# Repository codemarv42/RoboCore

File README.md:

# RoboCore

The RoboCore is basically a dual PCB solution, which is mounted on a chassis and takes over the evaluation and control of sensors and motors. Furthermore, this project was created by several people to develop the best robot for the RoboCup in the Rescue Line division. 

# Hardware

A combination of two PCBs is used as our hardware, where the main PCB (RoboCoreV3.2) is plugged onto a Raspberry Pi and therefore forms the main control unit. The second circuit board (RoboLightV4.2) is installed on the underside of the robot and is responsible for measuring the light values on the line track. Below is our current hardware combination.

## To do list

- [x] Find Upload issue
- [x] Implement Boot and EN Buttons
- [x] Find ADC issue when using Neopixel LEDs
- [x] Voltage state LEDs
- [x] Inconsistent red-green difference of the LEDs

## Changelog

RoboCore:

- V3.2: Remove Neopixel led because of ADC problems, better voltage regulator for motor driver and further power management features
- V3.1: Raspberry PI hat design, external Display and buttons as user interface, ESP32-S3, two motor driver, Neopixel LED, Voltage regulator update
- V2: MPU6050 as secound PCB, dual light sensor bar, Pullup Fix near buttons
- V1: Inital Version

RoboLight:

- V4.3: Swap FCP pinout
- V4.2: Use regular RGB LEDs instead, better LED and phototransistor arrangement
- V4.1: Use Neopixel RGB LEDs instead, remove center photo transistor
- V3: Control Leds individual via a shiftregister
- V2: Fix distance between inner photo transistors
- V1: Inital Version

## Control unit PCB

Parameter for PCB (RoboCoreV3.2):

- Layer: 4
- Thickness: 1,6mm
- Length: 65,05mm
- Height: 56,03mm
- Minimum Copper Trace Width: 0,125mm

Pinout:

## Light sensors PCB

Parameter for PCB (RoboLightV4.3):

- Layer: 2
- Thickness: 1,2mm / 1,6mm
- Length: 72,0mm
- Height: 15,23mm
- Minimum Copper Trace Width: 0,15mm

# Software

### You can find instructions for RoboCore V3.2 in PDF format here:
https://github.com/codemarv42/RoboCore/blob/main/Hardware/RoboCoreV3.2/RoboCoreV3.2%20Manual.pdf

## Required libraries

- Adafruit_GFX.h - https://github.com/adafruit/Adafruit-GFX-Library
- Adafruit_BusIO.h - https://github.com/adafruit/Adafruit_BusIO/tree/master
- Adafruit_PWMServoDriver.h - https://github.com/adafruit/Adafruit-PWM-Servo-Driver-Library
- Adafruit_SSD1306.h - https://github.com/adafruit/Adafruit_SSD1306
- MPU6050_light.h - https://github.com/rfetick/MPU6050_light
- VL53L1X.h - https://github.com/pololu/vl53l1x-arduino

## Download Mode

If no program can be uploaded to the ESP32-S3, it must be set to download mode. The following steps are necessary to do this:

1. Press and hold the BOOT and RESET button
2. Connect the RoboCore to the computer via USB
3. Release the RESET button while still holding the BOOT button
4. Release the BOOT button after a few seconds

## Compilation settings

To compile your program and then upload it to the RoboCore, some steps are necessary:

1. First you have to install the kernel of the ESP32 in Arduino: https://docs.espressif.com/projects/arduino-esp32/en/latest/installing.html
2. Next, the compilation settings must be specified. To do this, first select "ESP32S3 Dev Module" under Tools --> Board.
3. In the last step, the parameters of the ESP32 on the RoboCore must be set. To do this, select the following under Tools: 
- Board: "ESP32S3 Dev Module"
- USB CDC On Boot: "Enabled"
- CPU Frequency: "240MHz (WiFi/BT)"
- Flash Mode: "QIO 120MHz"
- Flash Size: "8MB (32Mb)"
- Partition Scheme: "8MB with SPIFFS"
- Erase all flash: "Disabled"
- Upload Speed: "921600"

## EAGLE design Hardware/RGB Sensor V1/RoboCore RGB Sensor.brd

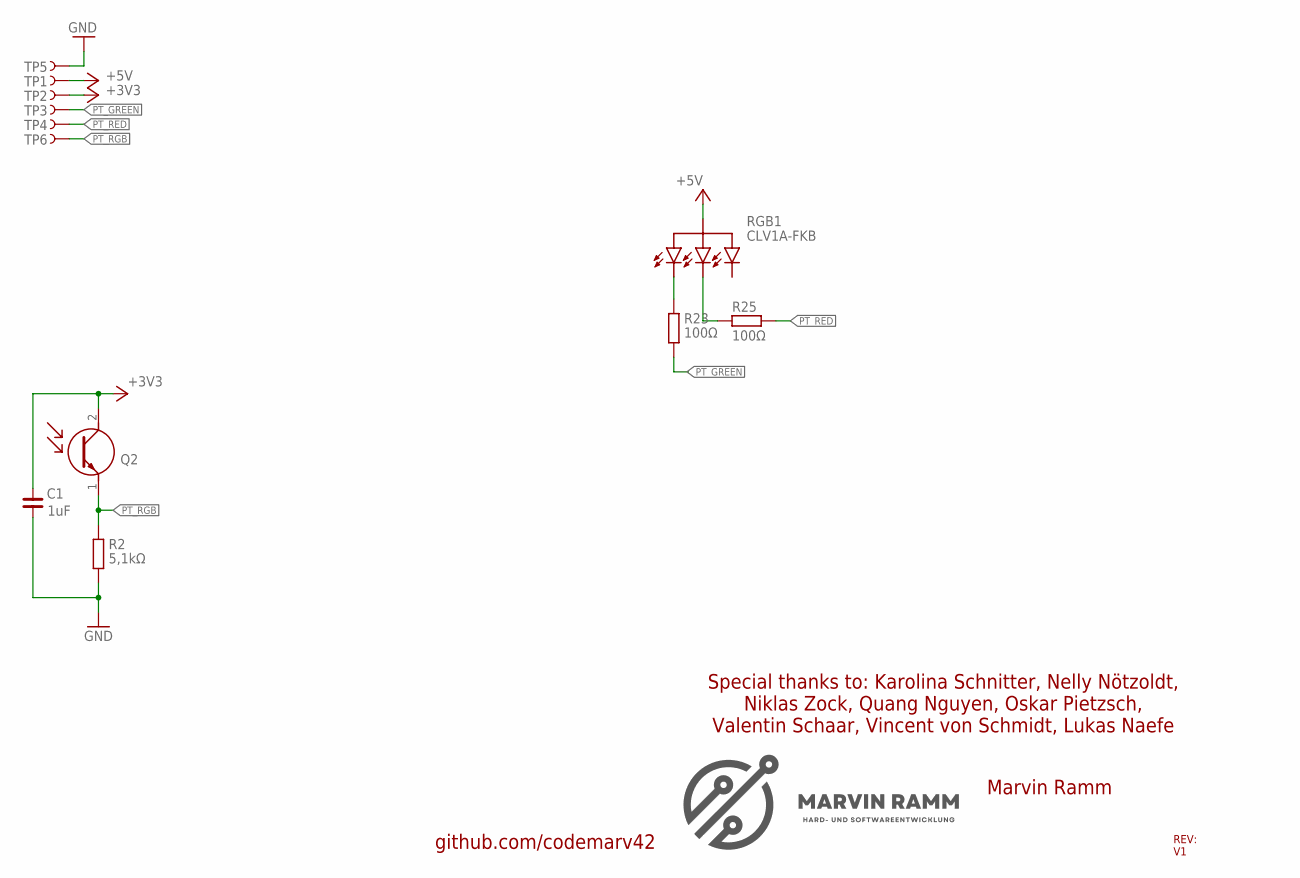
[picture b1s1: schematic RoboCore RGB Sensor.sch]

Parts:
C1: 1uF; C0402
Q2: PT17-21C/L41/TR8; 0805
R2: 5,1kΩ; R0402
R23, R25: 100Ω; R0402
RGB1: RGBLED
TP1, TP2, TP3, TP4, TP5, TP6: TEST-POINT3X5; PAD.03X.05

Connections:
+3V3: C1.2, Q2.2 (C), TP2.1
+5V: RGB1.+5V, TP1.1
GND: C1.1, R2.2, TP5.1
unnamed: R23.1, RGB1.P3
unnamed: R25.1, RGB1.P2
PT_GREEN: R23.2, TP3.1
PT_RED: R25.2, TP4.1
PT_RGB: Q2.1 (E), R2.1, TP6.1

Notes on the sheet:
RGB1
CLV1A-FKB
Marvin Ramm
REV: V1
github.com/codemarv42
Special thanks to: Karolina Schnitter, Nelly Nötzoldt, Niklas Zock, Quang Nguyen, Oskar Pietzsch, Valentin Schaar, Vincent von Schmidt, Lukas Naefe

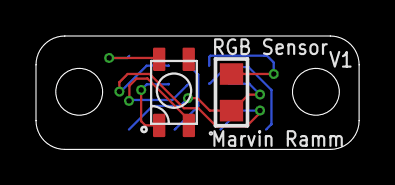
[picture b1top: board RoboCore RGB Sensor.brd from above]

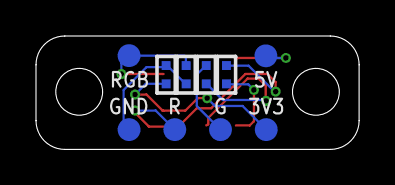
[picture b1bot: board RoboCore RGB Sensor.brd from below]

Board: 2 copper layers, 17.9 x 6.3 mm, 12 parts (10 on the bottom side), 8 nets.

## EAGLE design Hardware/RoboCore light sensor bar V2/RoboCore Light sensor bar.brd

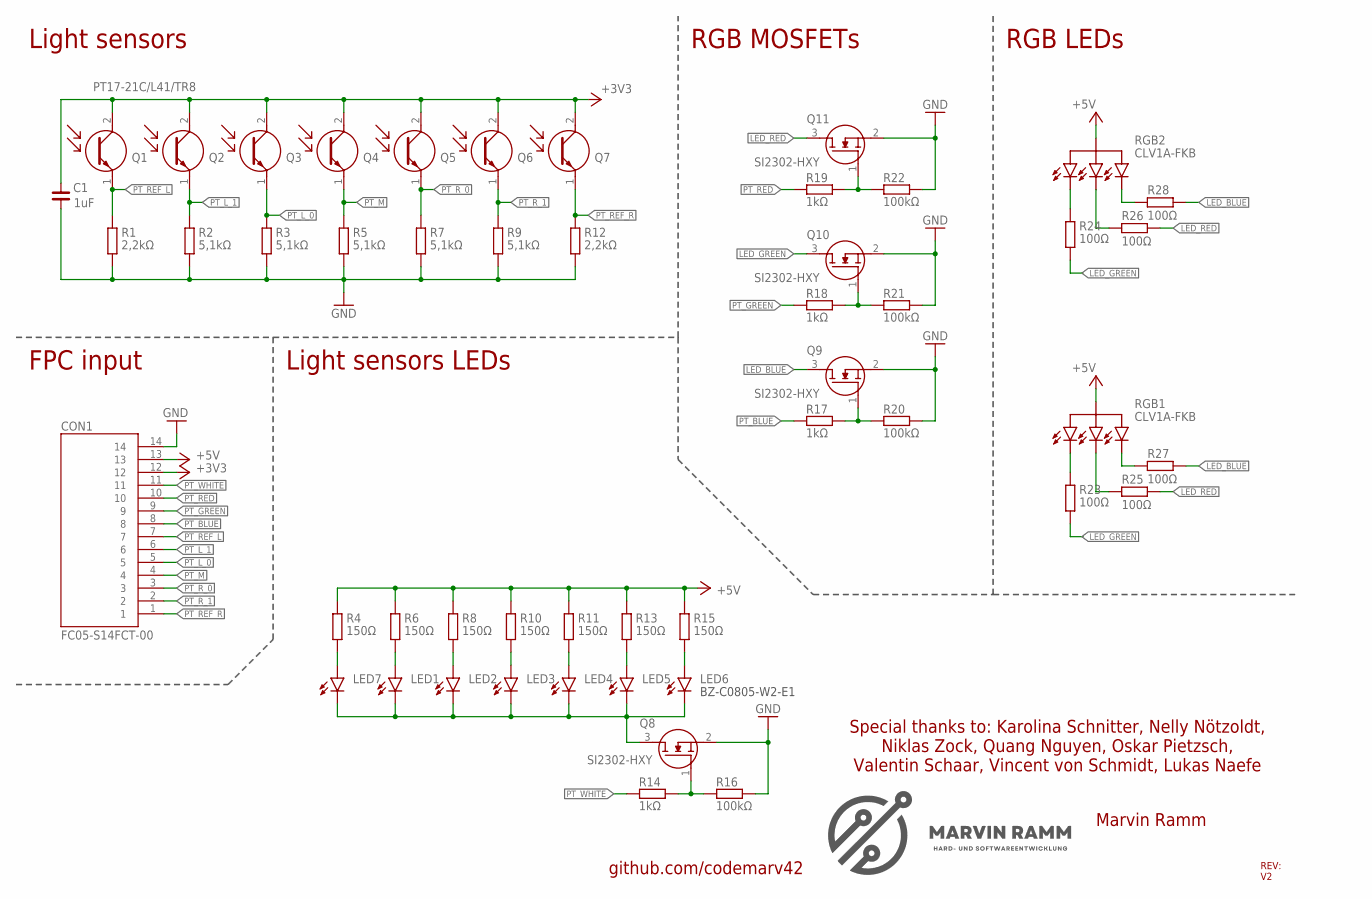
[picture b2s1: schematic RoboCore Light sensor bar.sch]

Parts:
C1: 1uF; C0402
CON1: FC05-S14FCT-00
LED1, LED2, LED3, LED4, LED5, LED6, LED7: LEDCHIP-LED0805; CHIP-LED0805
Q1, Q2, Q3, Q4, Q5, Q6, Q7: PT17-21C/L41/TR8; 0805
Q8, Q9, Q10, Q11: SI2302DDS-T1-GE3; SOT95P237X112-3N
R1, R12: 2,2kΩ; R0402
R2, R3, R5, R7, R9: 5,1kΩ; R0402
R4, R6, R8, R10, R11, R13, R15: 150Ω; R0402
R14, R17, R18, R19: 1kΩ; R0402
R16, R20, R21, R22: 100kΩ; R0402
R23, R24, R25, R26, R27, R28: 100Ω; R0402
RGB1, RGB2: RGBLED

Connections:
+3V3: C1.2, CON1.12, Q1.2 (C), Q2.2 (C), Q3.2 (C), Q4.2 (C), Q5.2 (C), Q6.2 (C), Q7.2 (C)
+5V: CON1.13, R4.1, R6.1, R8.1, R10.1, R11.1, R13.1, R15.1, RGB1.+5V, RGB2.+5V
GND: C1.1, CON1.14, Q8.2 (S), Q9.2 (S), Q10.2 (S), Q11.2 (S), R1.2, R2.2, R3.2, R5.2, R7.2, R9.2, R12.2, R16.2, R20.2, R21.2, R22.2
LED_BLUE: Q9.3 (D), R27.2, R28.2
LED_GREEN: Q10.3 (D), R23.2, R24.2
LED_RED: Q11.3 (D), R25.2, R26.2
unnamed: LED1.C, LED2.C, LED3.C, LED4.C, LED5.C, LED6.C, LED7.C, Q8.3 (D)
unnamed: LED7.A, R4.2
unnamed: Q11.1 (G), R19.2, R22.1
unnamed: Q10.1 (G), R18.2, R21.1
unnamed: Q9.1 (G), R17.2, R20.1
unnamed: LED5.A, R13.2
unnamed: LED6.A, R15.2
unnamed: Q8.1 (G), R14.2, R16.1
unnamed: LED4.A, R11.2
unnamed: R24.1, RGB2.P3
unnamed: R28.1, RGB2.P1
unnamed: R26.1, RGB2.P2
unnamed: R23.1, RGB1.P3
unnamed: R27.1, RGB1.P1
unnamed: R25.1, RGB1.P2
unnamed: LED3.A, R10.2
unnamed: LED2.A, R8.2
unnamed: LED1.A, R6.2
PT_BLUE: CON1.8, R17.1
PT_GREEN: CON1.9, R18.1
PT_L_0: CON1.5, Q3.1 (E), R3.1
PT_L_1: CON1.6, Q2.1 (E), R2.1
PT_M: CON1.4, Q4.1 (E), R5.1
PT_RED: CON1.10, R19.1
PT_REF_L: CON1.7, Q1.1 (E), R1.1
PT_REF_R: CON1.1, Q7.1 (E), R12.1
PT_R_0: CON1.3, Q5.1 (E), R7.1
PT_R_1: CON1.2, Q6.1 (E), R9.1
PT_WHITE: CON1.11, R14.1

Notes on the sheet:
Light sensors
RGB2
CLV1A-FKB
RGB1
Light sensors LEDs
SI2302-HXY
Marvin Ramm
REV: V2
github.com/codemarv42
FPC input
RGB MOSFETs
RGB LEDs
Special thanks to: Karolina Schnitter, Nelly Nötzoldt, Niklas Zock, Quang Nguyen, Oskar Pietzsch, Valentin Schaar, Vincent von Schmidt, Lukas Naefe
BZ-C0805-W2-E1

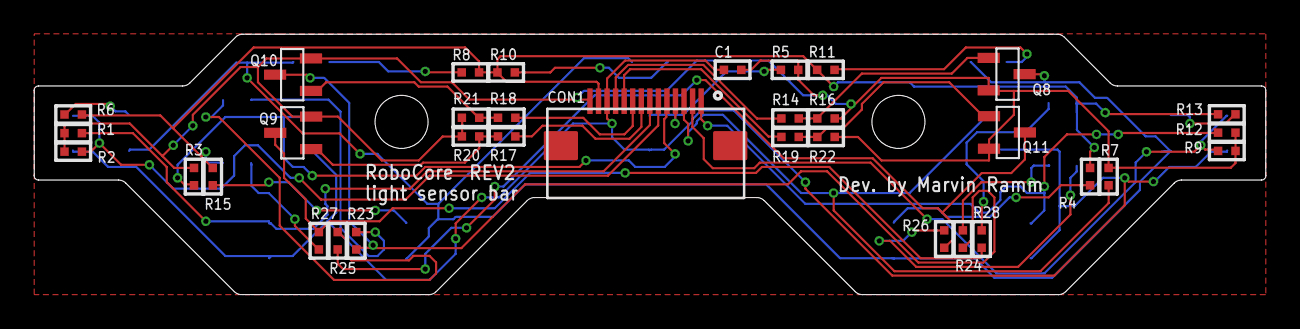
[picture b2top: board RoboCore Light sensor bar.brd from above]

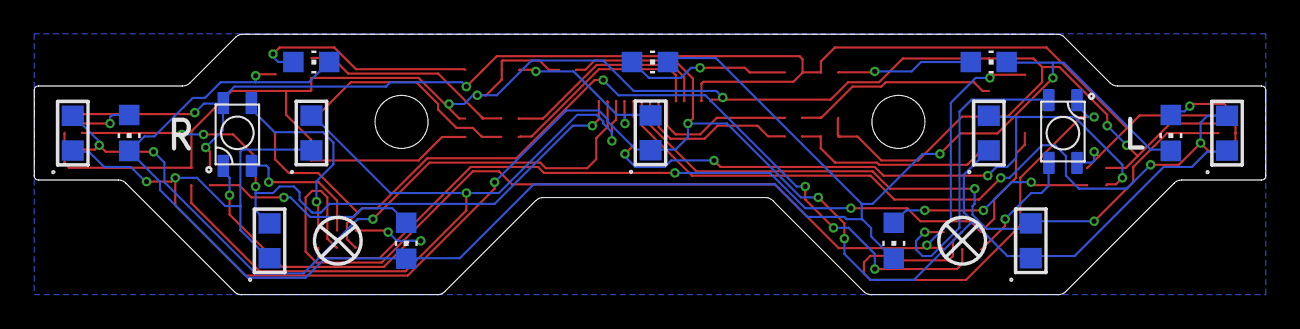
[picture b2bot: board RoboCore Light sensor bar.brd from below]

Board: 2 copper layers, 72.0 x 15.2 mm, 50 parts (16 on the bottom side), 35 nets.

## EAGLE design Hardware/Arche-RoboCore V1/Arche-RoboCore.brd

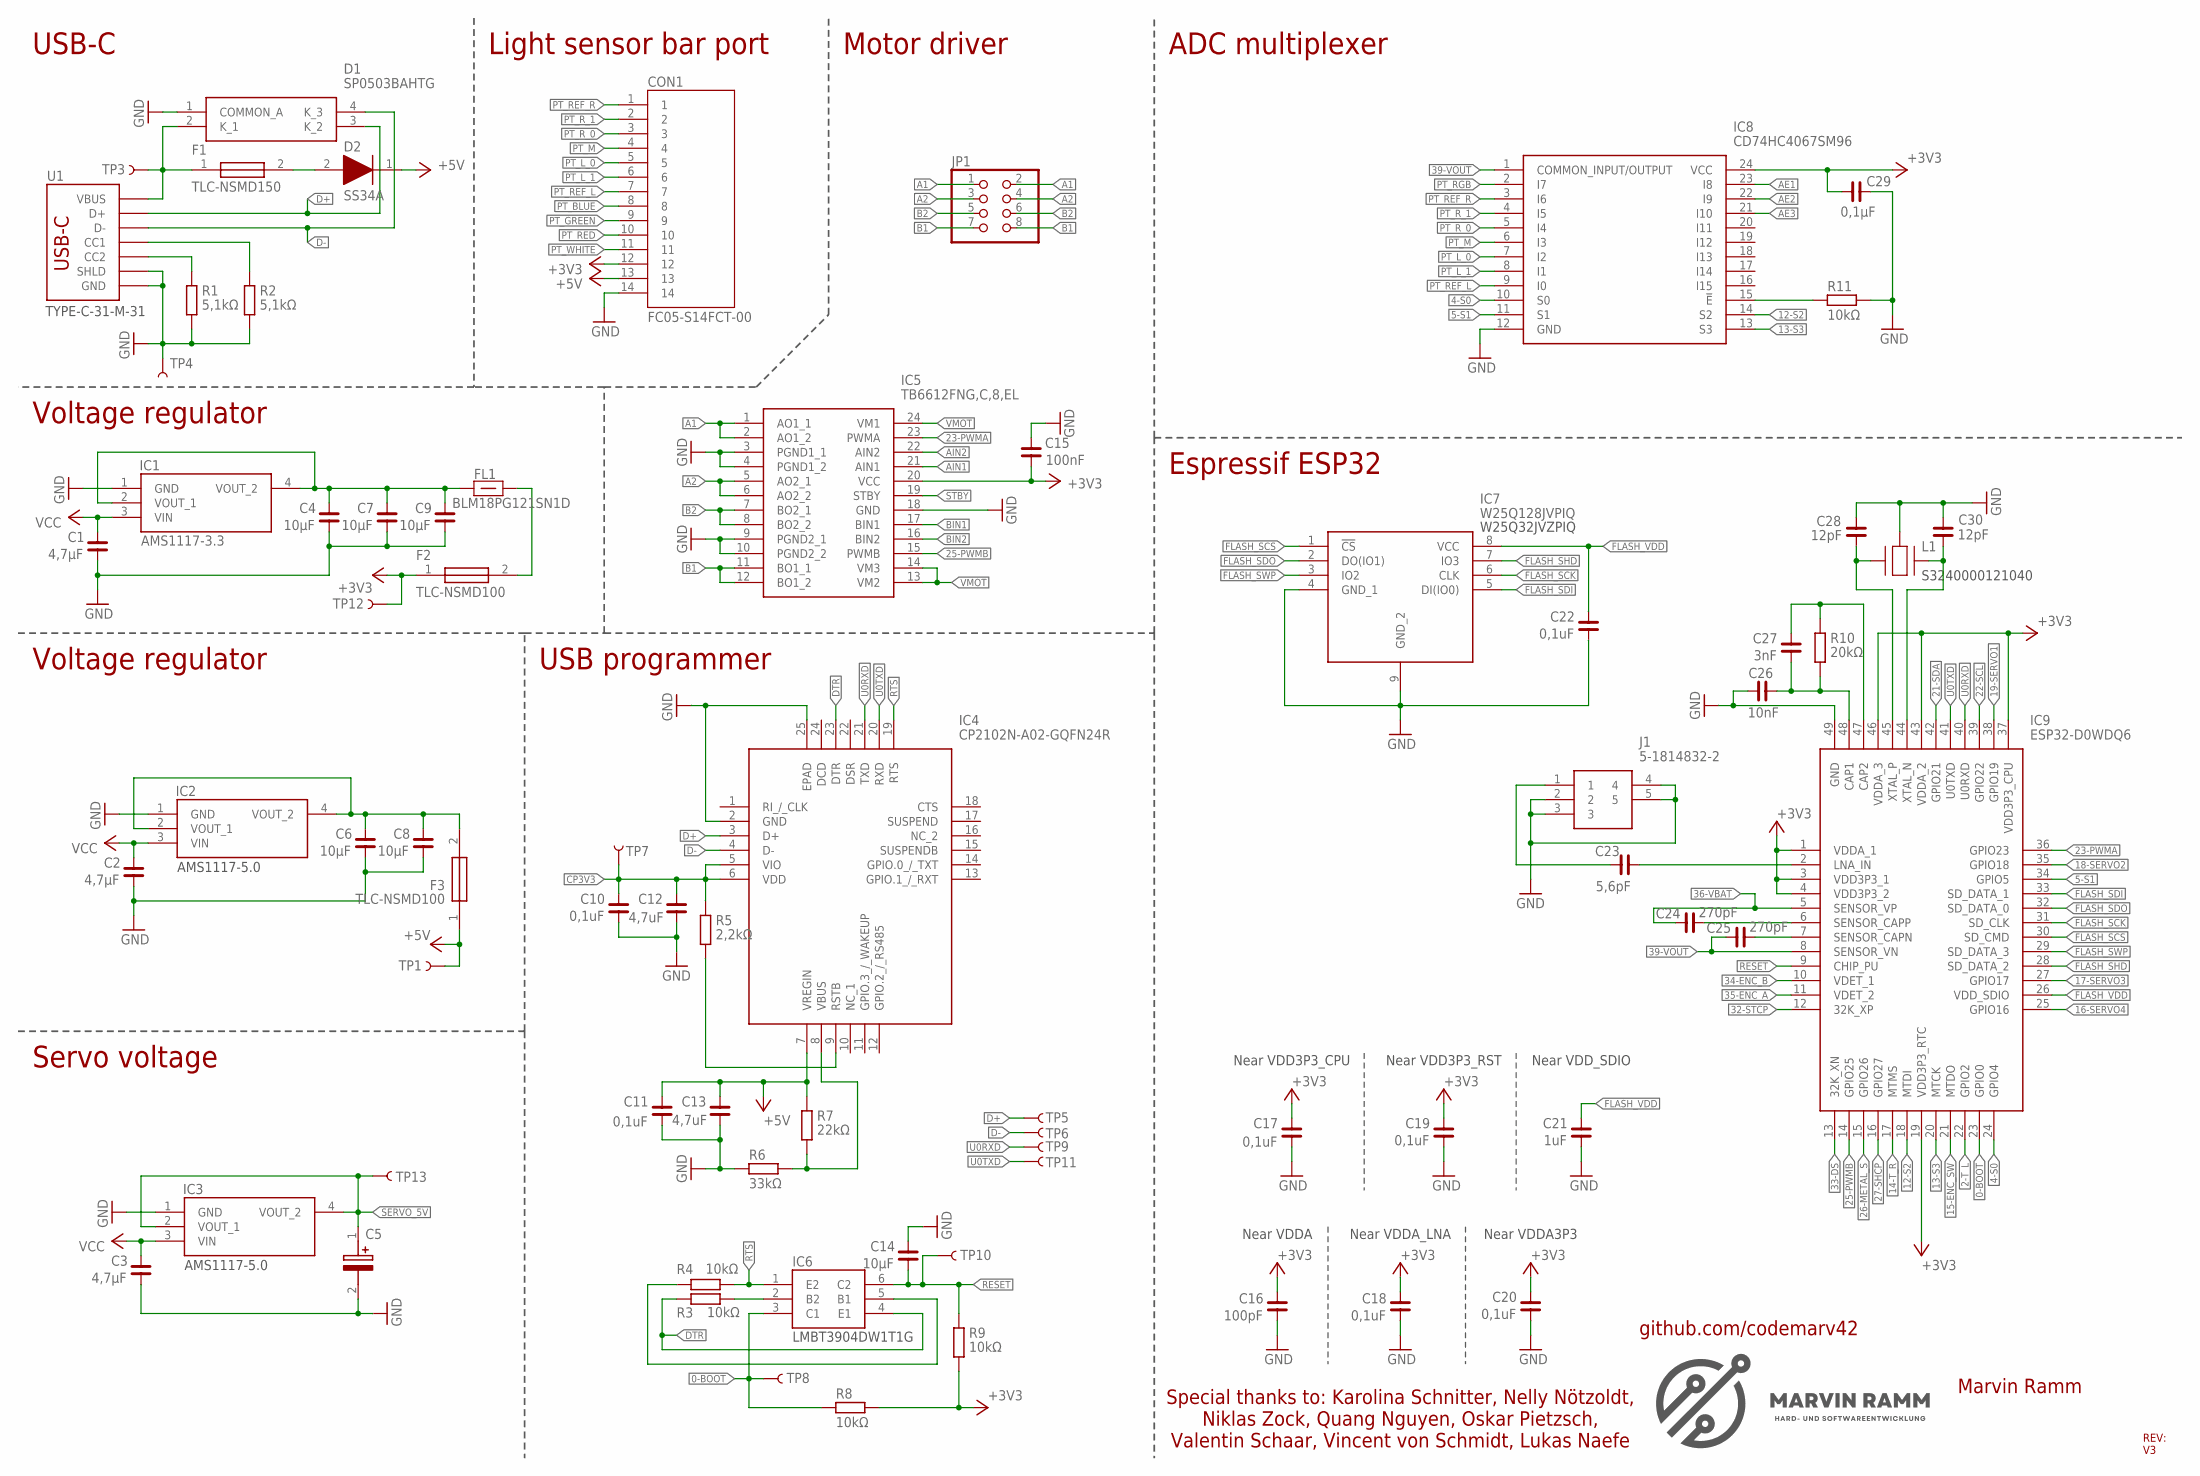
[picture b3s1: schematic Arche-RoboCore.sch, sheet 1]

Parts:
C1, C2, C3: 4,7µF; C0603
C4, C6, C7, C8, C9, C14: 10µF; C0603
C5: UUD1C151MCL1GS; CAPAE660X800N
C10, C11, C17, C18, C19, C20, C22: 0,1uF; C0402
C12, C13: 4,7uF; C0402
C15: 100nF; C0402
C16: 100pF; C0402
C21: 1uF; C0402
C23: 5,6pF; C0402
C24, C25: 270pF; C0402
C26: 10nF; C0402
C27: 3nF; C0402
C28, C30: 12pF; C0402
C29: 0,1µF; C0402
CON1: FC05-S14FCT-00
D1: SP0503BAHTG
D2: SS34A; DIOM5026X262N
F1, F2, F3: NANOSMDC020F-2; FUSC3216X82N
FL1: BLM18PG121SN1D; BLM18AG102BH1D
IC1, IC2, IC3: AMS1117-3.3; SOT229P700X180-4N
IC4: CP2102N-A02-GQFN24R; QFN50P400X400X80-25N
IC5: TB6612FNG,C,8,EL; SOP65P760X160-24N
IC6: MMDT3904-TP; SOT65P230X120-6N
IC7: W25Q128JVPIQ; SON127P800X600X80-9N
IC8: CD74HC4067SM96; SOP65P780X200-24N
IC9: ESP32-D0WDQ6; QFN40P600X600X90-49N
J1: 5-1814832-2; 518148322
JP1: PINHD-2X4; 2X04
L1: SMD-3225_4P16MHZ_20PF_10PPM_-4; SMD3225_4P16MHZ20PF10PPM4085
R1, R2: 5,1kΩ; R0402
R3, R4, R8, R9, R11: 10kΩ; R0402
R5: 2,2kΩ; R0402
R6: 33kΩ; R0402
R7: 22kΩ; R0402
R10: 20kΩ; R0402
TP1, TP3, TP4, TP5, TP6, TP7, TP8, TP9, TP10, TP11, TP12, TP13: TEST-POINT3X5; PAD.03X.05
U1: TYPE-C-31-M-14; TYPE-C-31-M-14_HRO

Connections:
0-BOOT: IC6.3 (C1), IC9.23 (GPIO0), R8.2, TP8.1
2-T_L: IC9.22 (GPIO2); also elsewhere on the board
4-S0: IC8.10 (S0), IC9.24 (GPIO4)
5-S1: IC8.11 (S1), IC9.34 (GPIO5)
12-S2: IC8.14 (S2), IC9.18 (MTDI)
13-S3: IC8.13 (S3), IC9.20 (MTCK)
14-T_R: IC9.17 (MTMS); also elsewhere on the board
15-ENC_SW: IC9.21 (MTDO); also elsewhere on the board
16-SERVO4: IC9.25 (GPIO16); also elsewhere on the board
17-SERVO3: IC9.27 (GPIO17); also elsewhere on the board
18-SERVO2: IC9.35 (GPIO18); also elsewhere on the board
19-SERVO1: IC9.38 (GPIO19); also elsewhere on the board
21-SDA: IC9.42 (GPIO21); also elsewhere on the board
22-SCL: IC9.39 (GPIO22); also elsewhere on the board
23-PWMA: IC5.23 (PWMA), IC9.36 (GPIO23)
25-PWMB: IC5.15 (PWMB), IC9.14 (GPIO25)
26-METAL_S: IC9.15 (GPIO26); also elsewhere on the board
27-SHCP: IC9.16 (GPIO27); also elsewhere on the board
32-STCP: IC9.12 (32K_XP); also elsewhere on the board
33-DS: IC9.13 (32K_XN); also elsewhere on the board
34-ENC_B: IC9.10 (VDET_1); also elsewhere on the board
35-ENC_A: IC9.11 (VDET_2); also elsewhere on the board
36-VBAT: C24.1, IC9.5 (SENSOR_VP); also elsewhere on the board
39-VOUT: C25.1, IC8.1 (COMMON_INPUT/OUTPUT), IC9.8 (SENSOR_VN)
+3V3: C15.1, C16.2, C17.2, C18.2, C19.2, C20.2, C29.1, CON1.12, F2.1, IC5.20 (VCC), IC8.24 (VCC), IC9.1 (VDDA_1), IC9.3 (VDD3P3_1), IC9.4 (VDD3P3_2), IC9.19 (VDD3P3_RTC), IC9.37 (VDD3P3_CPU), IC9.43 (VDDA_2), IC9.46 (VDDA_3), R8.1, R9.2, TP12.1; also elsewhere on the board
+5V: C11.2, C13.2, CON1.13, D2.1 (K), F3.1, IC4.7 (VREGIN), R7.1, TP1.1; also elsewhere on the board
A1: IC5.1 (AO1_1), IC5.2 (AO1_2), JP1.1, JP1.2
A2: IC5.5 (AO2_1), IC5.6 (AO2_2), JP1.3, JP1.4
AE1: IC8.23 (I8); also elsewhere on the board
AE2: IC8.22 (I9); also elsewhere on the board
AE3: IC8.21 (I10); also elsewhere on the board
AIN1: IC5.21 (AIN1); also elsewhere on the board
AIN2: IC5.22 (AIN2); also elsewhere on the board
B1: IC5.11 (BO1_1), IC5.12 (BO1_2), JP1.7, JP1.8
B2: IC5.7 (BO2_1), IC5.8 (BO2_2), JP1.5, JP1.6
BIN1: IC5.17 (BIN1); also elsewhere on the board
BIN2: IC5.16 (BIN2); also elsewhere on the board
CP3V3: C10.2, C12.2, IC4.5 (VIO), IC4.6 (VDD), R5.1, TP7.1
D+: D1.3 (K_2), IC4.3 (D+), TP5.1, U1.A6 (D+), U1.B6 (D+)
D-: D1.4 (K_3), IC4.4 (D-), TP6.1, U1.A7 (D-), U1.B7 (D-)
DTR: IC4.23 (DTR), IC6.4 (E1), R3.2
FLASH_SCK: IC7.6 (CLK), IC9.31 (SD_CLK)
FLASH_SCS: IC7.1 (!CS), IC9.30 (SD_CMD)
FLASH_SDI: IC7.5 (DI(IO0)), IC9.33 (SD_DATA_1)
FLASH_SDO: IC7.2 (DO(IO1)), IC9.32 (SD_DATA_0)
FLASH_SHD: IC7.7 (IO3), IC9.28 (SD_DATA_2)
FLASH_SWP: IC7.3 (IO2), IC9.29 (SD_DATA_3)
FLASH_VDD: C21.2, C22.2, IC7.8 (VCC), IC9.26 (VDD_SDIO)
GND: C1.2, C2.2, C3.2, C4.2, C5.2 (-), C6.2, C7.2, C8.2, C9.2, C10.1, C11.1, C12.1, C13.1, C14.1, C15.2, C16.1, C17.1, C18.1, C19.1, C20.1, C21.1, C22.1, C26.1, C28.1, C29.2, C30.1, CON1.14, D1.1 (COMMON_A), IC1.1 (GND), IC2.1 (GND), IC3.1 (GND), IC4.2 (GND), IC4.25 (EPAD), IC5.3 (PGND1_1), IC5.4 (PGND1_2), IC5.9 (PGND2_1), IC5.10 (PGND2_2), IC5.18 (GND), IC7.4 (GND_1), IC7.9 (GND_2), IC8.12 (GND), IC9.49 (GND), J1.2, J1.3, J1.4, J1.5, L1.2 (GND_2), L1.4 (GND_2), R1.2, R2.2, R6.2, R11.2, TP4.1, U1.A1B12 (GND), U1.B1A12 (GND), U1.P$1 (SHLD), U1.P$2 (SHLD), U1.P$3 (SHLD), U1.P$4 (SHLD), U1.P$5 (SHLD), U1.P$6 (SHLD), U1.P$7 (SHLD), U1.P$8 (SHLD), U1.P$9 (SHLD), U1.P$10 (SHLD), U1.P$11 (SHLD), U1.P$12 (SHLD), U1.P$14 (SHLD), U1.P$16 (SHLD), U1.P$18 (SHLD), U1.P$20 (SHLD); also elsewhere on the board
unnamed: D2.2 (A), F1.2
unnamed: C6.1, C8.1, F3.2, IC2.2 (VOUT_1), IC2.4 (VOUT_2)
unnamed: F2.2, FL1.1
unnamed: C4.1, C7.1, C9.1, FL1.2, IC1.2 (VOUT_1), IC1.4 (VOUT_2)
unnamed: R1.1, U1.B5 (CC2)
unnamed: R2.1, U1.A5 (CC1)
unnamed: IC4.9 (RSTB), R5.2
unnamed: IC4.8 (VBUS), R6.1, R7.2
unnamed: IC8.15 (!E), R11.1
unnamed: C23.1, IC9.2 (LNA_IN)
unnamed: C26.2, C27.1, IC9.48 (CAP1), R10.2
unnamed: C27.2, IC9.47 (CAP2), R10.1
unnamed: C30.2, IC9.44 (XTAL_N), L1.3 (CRYSTAL_2)
unnamed: C28.2, IC9.45 (XTAL_P), L1.1 (CRYSTAL_1)
unnamed: C23.2, J1.1
unnamed: IC6.5 (B1), R4.2
unnamed: IC6.2 (B2), R3.1
unnamed: C25.2, IC9.7 (SENSOR_CAPN)
unnamed: C24.2, IC9.6 (SENSOR_CAPP)
PT_BLUE: CON1.8; also elsewhere on the board
PT_GREEN: CON1.9; also elsewhere on the board
PT_L_0: CON1.5, IC8.7 (I2)
PT_L_1: CON1.6, IC8.8 (I1)
PT_M: CON1.4, IC8.6 (I3)
PT_RED: CON1.10; also elsewhere on the board
PT_REF_L: CON1.7, IC8.9 (I0)
PT_REF_R: CON1.1, IC8.3 (I6)
PT_RGB: IC8.2 (I7); also elsewhere on the board
PT_R_0: CON1.3, IC8.5 (I4)
PT_R_1: CON1.2, IC8.4 (I5)
PT_WHITE: CON1.11; also elsewhere on the board
RESET: C14.2, IC6.6 (C2), IC9.9 (CHIP_PU), R9.1, TP10.1
RTS: IC4.19 (RTS), IC6.1 (E2), R4.1
SERVO_5V: C5.1 (+), IC3.2 (VOUT_1), IC3.4 (VOUT_2), TP13.1; also elsewhere on the board
STBY: IC5.19 (STBY); also elsewhere on the board
U0RXD: IC4.21 (TXD), IC9.40 (U0RXD), TP9.1
U0TXD: IC4.20 (RXD), IC9.41 (U0TXD), TP11.1
USBDIRECT: D1.2 (K_1), F1.1, TP3.1, U1.A4B9 (VBUS), U1.B4A9 (VBUS)
VCC: C1.1, C2.1, C3.1, IC1.3 (VIN), IC2.3 (VIN), IC3.3 (VIN); also elsewhere on the board
VMOT: IC5.13 (VM2), IC5.14 (VM3), IC5.24 (VM1); also elsewhere on the board

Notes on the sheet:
AMS1117-5.0
S3240000121040
Near VDDA
Near VDDA_LNA
Near VDDA3P3
Near VDD3P3_CPU
Near VDD3P3_RST
Near VDD_SDIO
W25Q32JVZPIQ
TYPE-C-31-M-31
TLC-NSMD150
LMBT3904DW1T1G
Marvin Ramm
REV: V3
USB-C
ADC multiplexer
Espressif ESP32
Voltage regulator
USB programmer
github.com/codemarv42
TLC-NSMD100
Motor driver
Light sensor bar port
Servo voltage
Special thanks to: Karolina Schnitter, Nelly Nötzoldt, Niklas Zock, Quang Nguyen, Oskar Pietzsch, Valentin Schaar, Vincent von Schmidt, Lukas Naefe

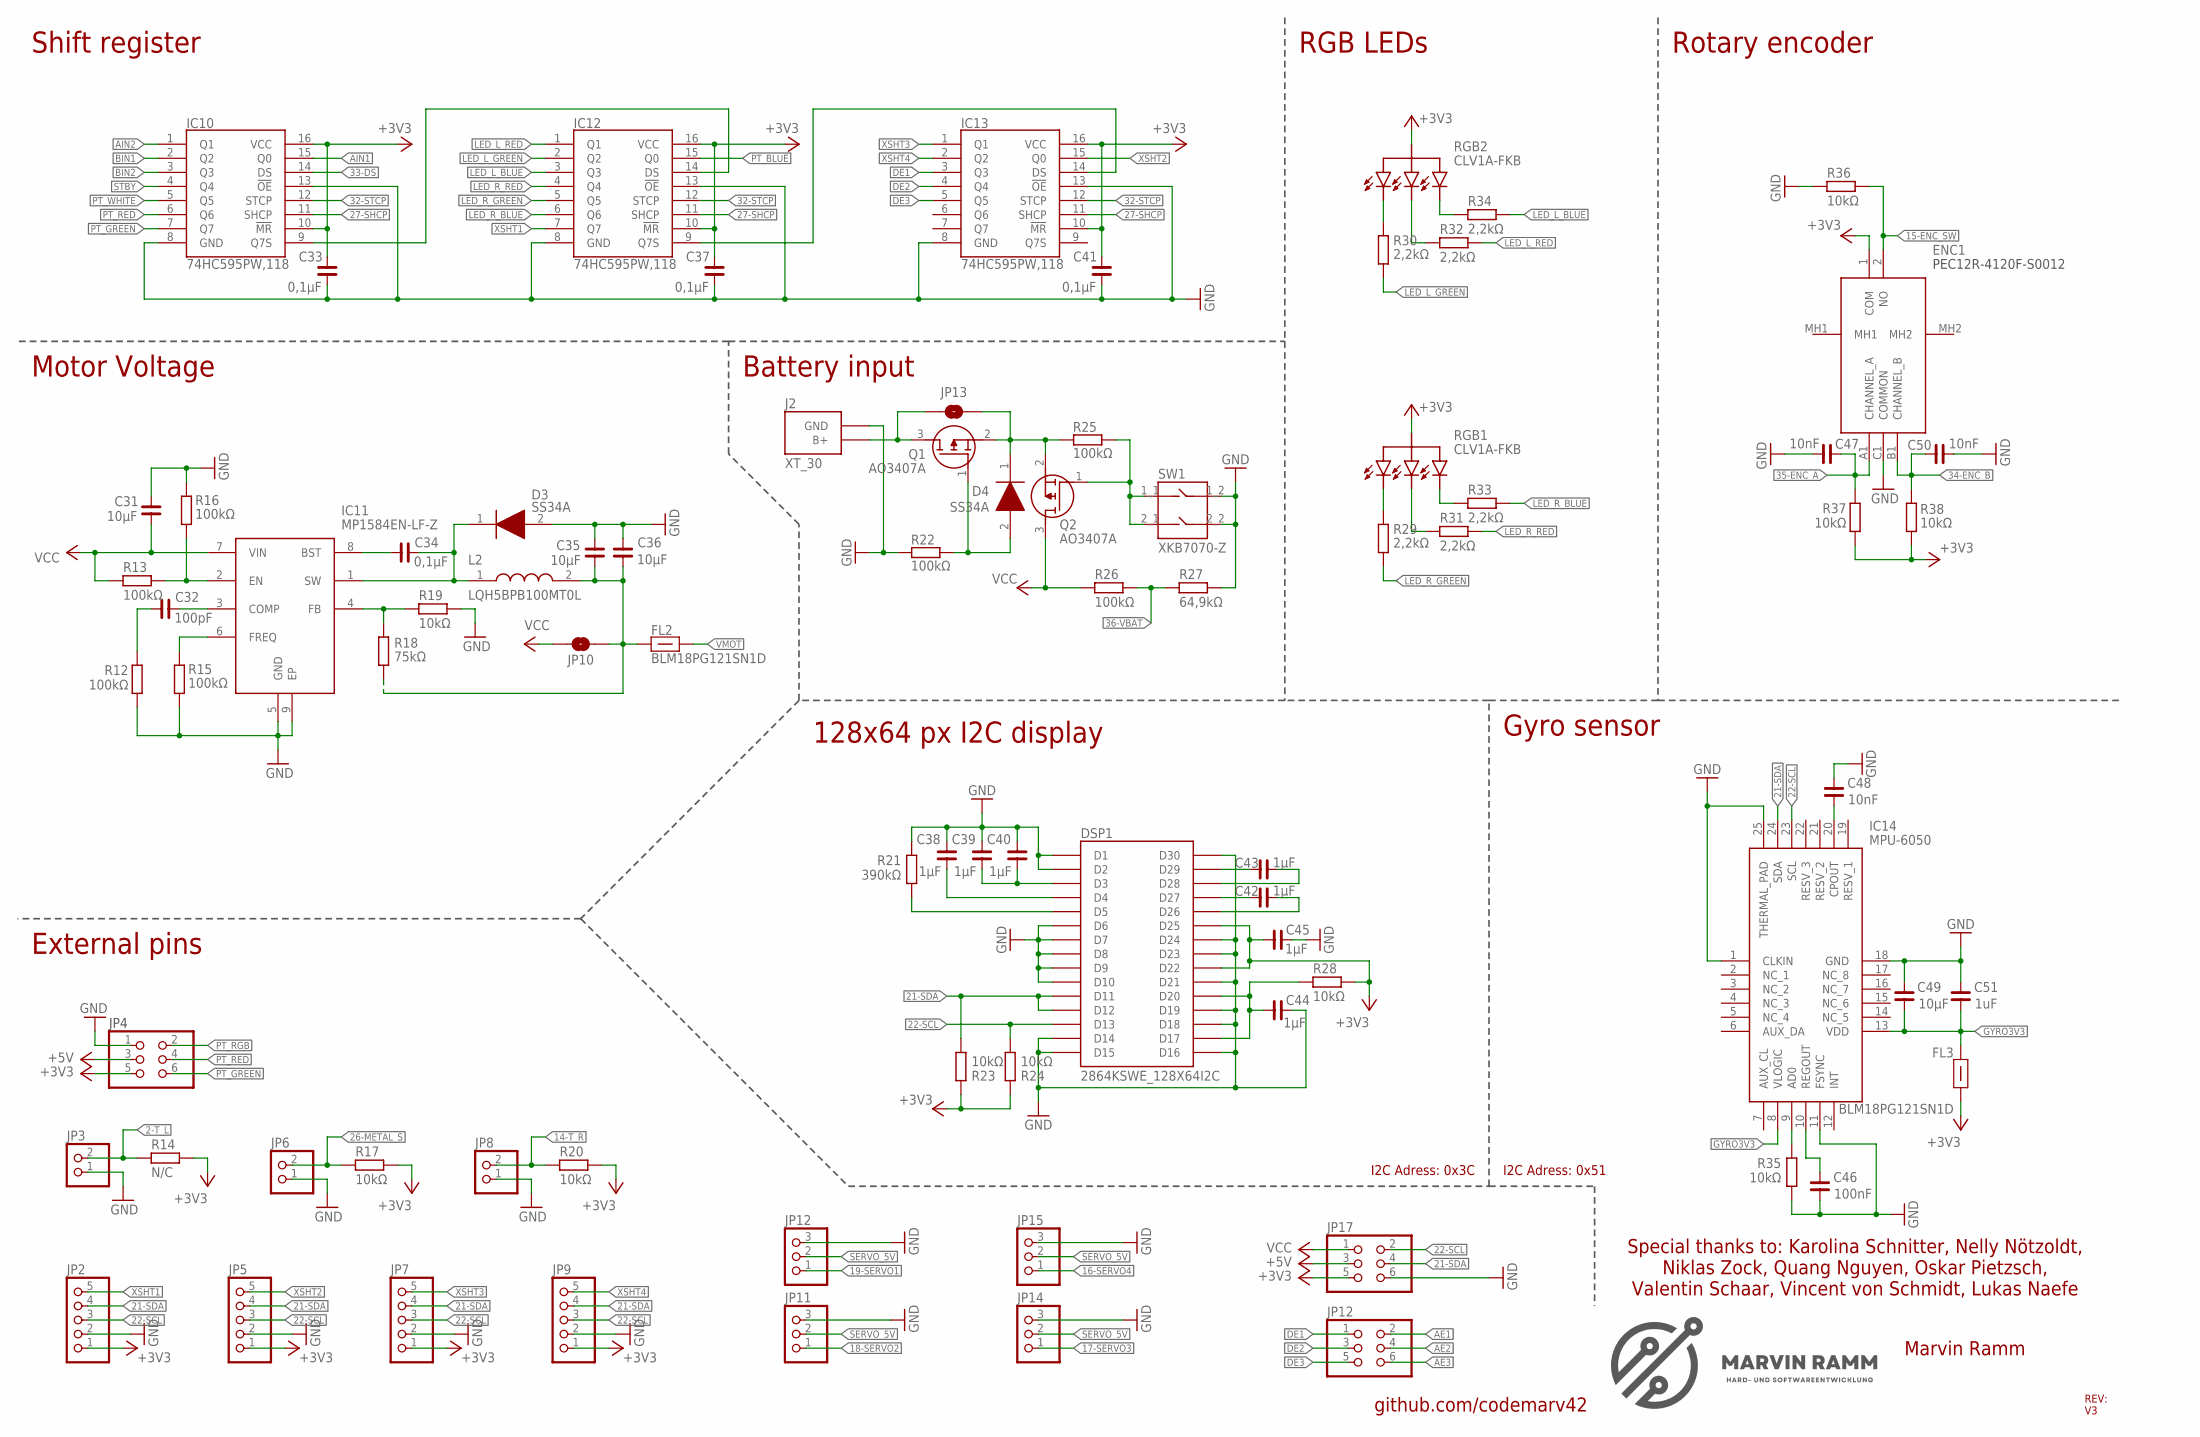
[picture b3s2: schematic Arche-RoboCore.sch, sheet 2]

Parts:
C31, C35, C36, C49: 10µF; C0603
C32: 100pF; C0402
C33, C34, C37, C41: 0,1µF; C0402
C38, C39, C40, C42, C43, C44, C45: 1µF; C0402
C46: 100nF; C0402
C47, C48, C50: 10nF; C0402
C51: 1uF; C0402
D3, D4: SS34A; DIOM5026X262N
DSP1: 2864KSWE_128X64I2C
ENC1: PEC12R-4230F-S0024; PEC12R4230FS0024
FL2, FL3: BLM18PG121SN1D; BLM18AG102BH1D
IC10, IC12, IC13: 74HC595PW,118; SOP65P640X110-16N
IC11: MP1584EN-LF-Z; SOIC127P600X170-9N
IC14: MPU-6050; QFN50P400X400X95-25N
J2: XT_30
JP2, JP5, JP7, JP9: PINHD-1X5; 1X05
JP3, JP6, JP8: PINHD-1X2; 1X02
JP4, JP16, JP17: PINHD-2X3; 2X03
JP10, JP13: JUMPER-SMT_2_NO_SILK; SMT-JUMPER_2_NO_SILK
JP11, JP12, JP14, JP15: PINHD-1X3; 1X03
L2: LQH5BPB100MT0L
Q1, Q2: AO3407A; SOT95P280X125-3N
R12, R13, R15, R16, R22, R25, R26: 100kΩ; R0402
R14: N/C; R0402
R17, R19, R20, R23, R24, R28, R35, R36, R37, R38: 10kΩ; R0402
R18: 75kΩ; R0402
R21: 390kΩ; R0402
R27: 64,9kΩ; R0402
R29, R30, R31, R32, R33, R34: 2,2kΩ; R0402
RGB1, RGB2: RGBLED
SW1: XKB7070-Z

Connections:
2-T_L: JP3.2, R14.1; also elsewhere on the board
14-T_R: JP8.2, R20.1; also elsewhere on the board
15-ENC_SW: ENC1.2 (NO), R36.2; also elsewhere on the board
16-SERVO4: JP15.1; also elsewhere on the board
17-SERVO3: JP14.1; also elsewhere on the board
18-SERVO2: JP11.1; also elsewhere on the board
19-SERVO1: JP12.1; also elsewhere on the board
21-SDA: DSP1.D11, DSP1.D12, IC14.24 (SDA), JP2.4, JP5.4, JP7.4, JP9.4, JP17.4, R23.1; also elsewhere on the board
22-SCL: DSP1.D13, IC14.23 (SCL), JP2.3, JP5.3, JP7.3, JP9.3, JP17.2, R24.1; also elsewhere on the board
26-METAL_S: JP6.2, R17.1; also elsewhere on the board
27-SHCP: IC10.11 (SHCP), IC12.11 (SHCP), IC13.11 (SHCP); also elsewhere on the board
32-STCP: IC10.12 (STCP), IC12.12 (STCP), IC13.12 (STCP); also elsewhere on the board
33-DS: IC10.14 (DS); also elsewhere on the board
34-ENC_B: C50.1, ENC1.B1 (CHANNEL_B), R38.2; also elsewhere on the board
35-ENC_A: C47.1, ENC1.A1 (CHANNEL_A), R37.2; also elsewhere on the board
36-VBAT: R26.2, R27.1; also elsewhere on the board
+3V3: C33.1, C37.1, C41.1, C45.1, DSP1.D22, DSP1.D25, ENC1.1 (COM), FL3.1, IC10.10 (!MR), IC10.16 (VCC), IC12.10 (!MR), IC12.16 (VCC), IC13.10 (!MR), IC13.16 (VCC), JP2.1, JP4.5, JP5.1, JP7.1, JP9.1, JP17.5, R14.2, R17.2, R20.2, R23.2, R24.2, R28.2, R37.1, R38.1, RGB1.+5V, RGB2.+5V; also elsewhere on the board
+5V: JP4.3, JP17.3; also elsewhere on the board
AE1: JP16.2; also elsewhere on the board
AE2: JP16.4; also elsewhere on the board
AE3: JP16.6; also elsewhere on the board
AIN1: IC10.15 (Q0); also elsewhere on the board
AIN2: IC10.1 (Q1); also elsewhere on the board
BIN1: IC10.2 (Q2); also elsewhere on the board
BIN2: IC10.3 (Q3); also elsewhere on the board
DE1: IC13.3 (Q3), JP16.1
DE2: IC13.4 (Q4), JP16.3
DE3: IC13.5 (Q5), JP16.5
GND: C31.1, C33.2, C35.1, C36.1, C37.2, C38.1, C39.1, C40.1, C41.2, C44.2, C45.2, C46.1, C47.2, C48.2, C49.1, C50.2, C51.2, D3.2 (A), DSP1.D1, DSP1.D2, DSP1.D6, DSP1.D7, DSP1.D8, DSP1.D9, DSP1.D10, DSP1.D14, DSP1.D15, DSP1.D16, DSP1.D18, DSP1.D19, DSP1.D21, DSP1.D23, DSP1.D24, DSP1.D30, ENC1.C1 (COMMON), IC10.8 (GND), IC10.13 (!OE), IC11.5 (GND), IC11.9 (EP), IC12.8 (GND), IC12.13 (!OE), IC13.8 (GND), IC13.13 (!OE), IC14.1 (CLKIN), IC14.11 (FSYNC), IC14.18 (GND), IC14.25 (THERMAL_PAD), J2.GND, JP2.2, JP3.1, JP4.1, JP5.2, JP6.1, JP7.2, JP8.1, JP9.2, JP11.3, JP12.3, JP14.3, JP15.3, JP17.6, R12.2, R15.2, R16.1, R19.1, R21.2, R22.1, R27.2, R35.1, R36.1, SW1.1_2, SW1.2_2; also elsewhere on the board
GYRO3V3: C49.2, C51.1, FL3.2, IC14.8 (VLOGIC), IC14.13 (VDD)
LED_L_BLUE: IC12.3 (Q3), R34.2
LED_L_GREEN: IC12.2 (Q2), R30.2
LED_L_RED: IC12.1 (Q1), R32.2
LED_R_BLUE: IC12.6 (Q6), R33.2
LED_R_GREEN: IC12.5 (Q5), R29.2
LED_R_RED: IC12.4 (Q4), R31.2
unnamed: C48.1, IC14.20 (CPOUT)
unnamed: C46.2, IC14.10 (REGOUT)
unnamed: IC14.9 (AD0), R35.2
unnamed: Q2.1 (G), R25.2, SW1.1_1, SW1.2_1
unnamed: IC12.9 (Q7S), IC13.14 (DS)
unnamed: D4.1 (K), JP13.1, Q1.2 (S), Q2.2 (S), R25.1
unnamed: D4.2 (A), Q1.1 (G), R22.2
unnamed: J2.B+, JP13.2, Q1.3 (D)
unnamed: C35.2, C36.2, FL2.2, JP10.1, L2.2, R18.2
unnamed: IC11.2 (EN), R13.1, R16.2
unnamed: IC11.6 (FREQ), R15.1
unnamed: C32.2, IC11.3 (COMP)
unnamed: C42.1, DSP1.D27
unnamed: C44.1, DSP1.D17, DSP1.D20, R28.1
unnamed: C38.2, DSP1.D4
unnamed: C42.2, DSP1.D26
unnamed: C39.2, C40.2, DSP1.D3
unnamed: DSP1.D5, R21.1
unnamed: C43.1, DSP1.D29
unnamed: C43.2, DSP1.D28
unnamed: C32.1, R12.1
unnamed: C34.2, D3.1 (K), IC11.1 (SW), L2.1
unnamed: R30.1, RGB2.P3
unnamed: R34.1, RGB2.P1
unnamed: R32.1, RGB2.P2
unnamed: C34.1, IC11.8 (BST)
unnamed: IC10.9 (Q7S), IC12.14 (DS)
unnamed: R29.1, RGB1.P3
unnamed: R33.1, RGB1.P1
unnamed: R31.1, RGB1.P2
unnamed: IC11.4 (FB), R18.1, R19.2
PT_BLUE: IC12.15 (Q0); also elsewhere on the board
PT_GREEN: IC10.7 (Q7), JP4.6; also elsewhere on the board
PT_RED: IC10.6 (Q6), JP4.4; also elsewhere on the board
PT_RGB: JP4.2; also elsewhere on the board
PT_WHITE: IC10.5 (Q5); also elsewhere on the board
SERVO_5V: JP11.2, JP12.2, JP14.2, JP15.2; also elsewhere on the board
STBY: IC10.4 (Q4); also elsewhere on the board
VCC: C31.2, IC11.7 (VIN), JP10.2, JP17.1, Q2.3 (D), R13.2, R26.1; also elsewhere on the board
VMOT: FL2.1; also elsewhere on the board
XSHT1: IC12.7 (Q7), JP2.5
XSHT2: IC13.15 (Q0), JP5.5
XSHT3: IC13.1 (Q1), JP7.5
XSHT4: IC13.2 (Q2), JP9.5

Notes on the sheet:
RGB2
CLV1A-FKB
Marvin Ramm
REV: V3
Gyro sensor
Rotary encoder
External pins
128x64 px I2C display
I2C Adress: 0x51
PEC12R-4120F-S0012
RGB1
RGB LEDs
github.com/codemarv42
JP12
I2C Adress: 0x3C
Motor Voltage
Shift register
Battery input
JP4
Special thanks to: Karolina Schnitter, Nelly Nötzoldt, Niklas Zock, Quang Nguyen, Oskar Pietzsch, Valentin Schaar, Vincent von Schmidt, Lukas Naefe

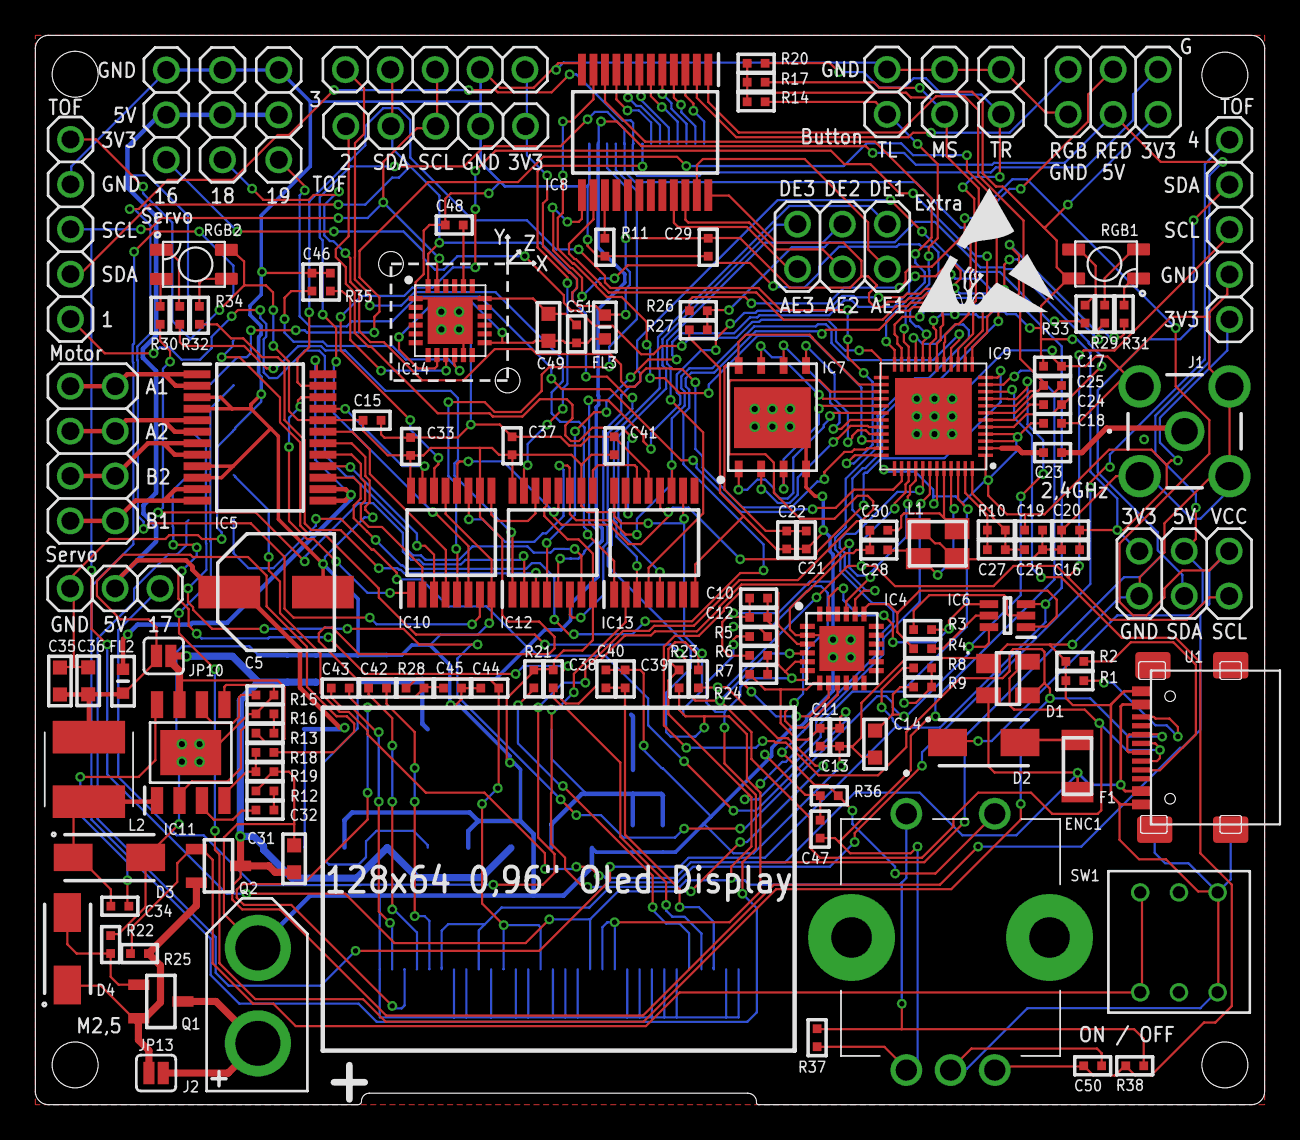
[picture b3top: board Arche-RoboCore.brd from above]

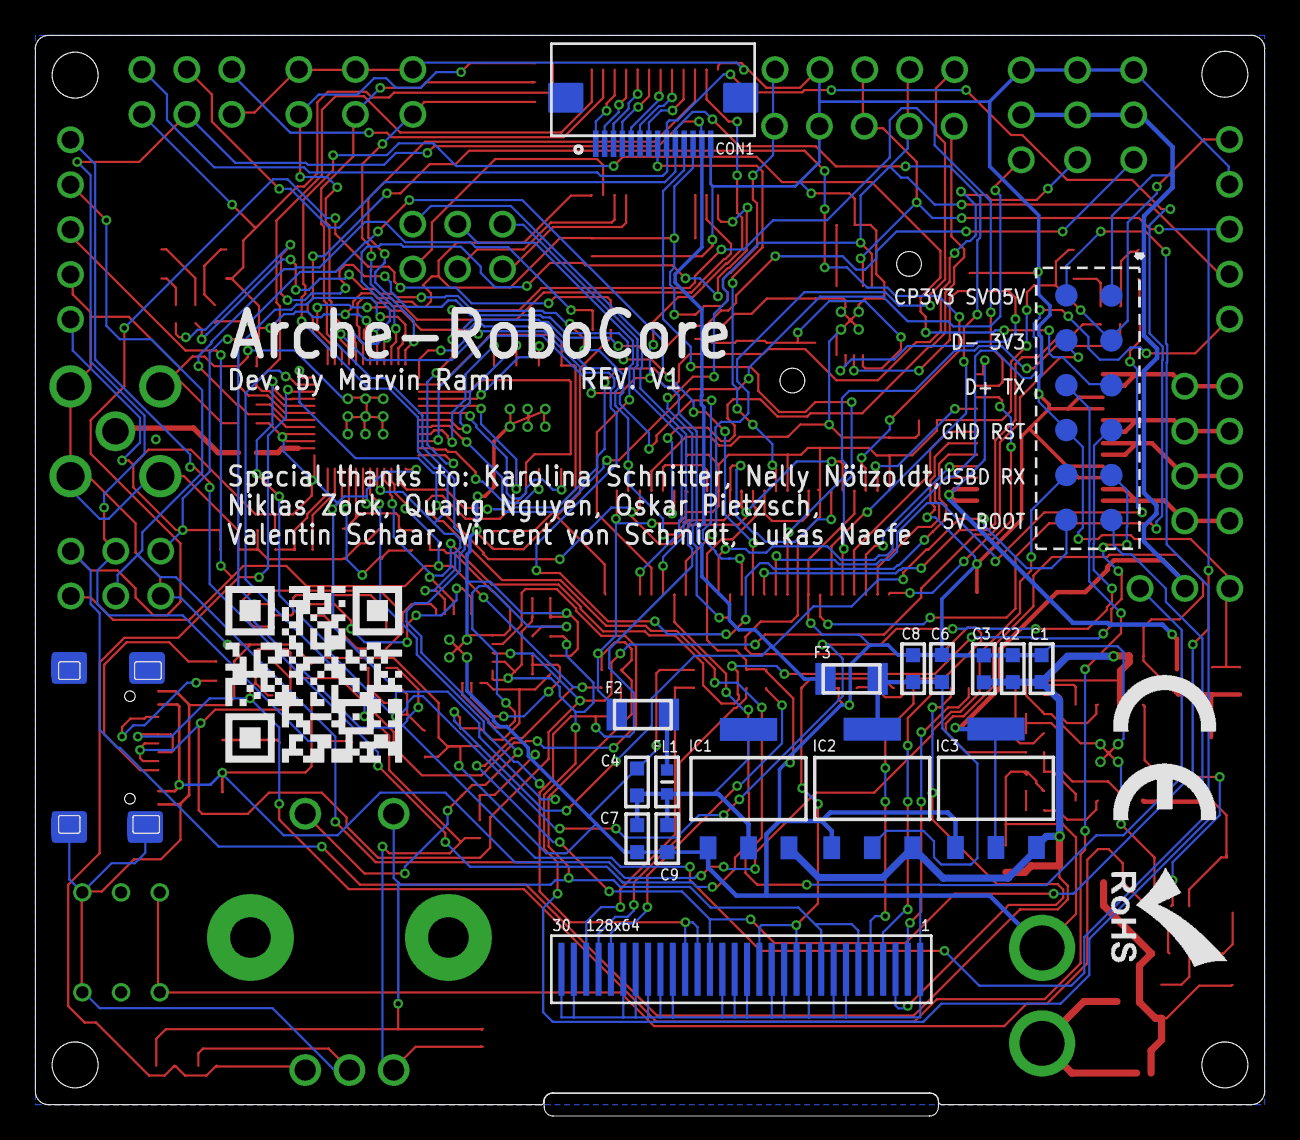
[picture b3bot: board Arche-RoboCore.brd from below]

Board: 2 copper layers, 69.5 x 60.5 mm, 155 parts (28 on the bottom side), 134 nets.

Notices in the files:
parts and their libraries:
rc-master-smd: Copyright (C) 2007, Bob Starr
SparkFun-Jumpers: Licensing: Creative Commons ShareAlike 4.0 International - https://creativecommons.org/licenses/by-sa/4.0
COPYRIGHT: Copyright (C) 2018 Accelerated Designs. All rights reserved
